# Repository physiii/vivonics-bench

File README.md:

# Vivonics Bench

Standalone hardware-bench repository for Vivonics shared-optical-metrology and
operator-material-screen work. The parent Vivonics repo consumes this
repository as its `bench/` Git submodule. It owns
both the Raspberry Pi measurement service and the ESP32-S3 laser-controller
firmware/circuit package.

The Pi owns the tight first-loop instrumentation:

- HDMI projector pattern display
- `IMX477` camera capture through `rpicam` / RTSP frame grabs
- USB-first control and telemetry for the ESP32-S3 four-source laser controller,
  with automatic Wi-Fi fallback
- optional `TSL2591` and `AS7341` I2C sensor snapshots
- later BPW34 photodiode data only after an ESP32/external ADC or TIA path

## Files

- `bench_service.py`: FastAPI service for projector/camera/sensor runs.
- `x1_measurement.py`: file-backed CLI smoke-test runner.
- `capture.py`, `projector.py`, `sensors.py`: hardware adapters.
- `laser_gpio.py`: Raspberry Pi GPIO outputs for red / green laser switching.
- `laser_controller_client.py`: persistent USB owner, normalized ADC telemetry,
  independent four-source control, and Wi-Fi fallback.
- `photocycle.py`: metrology and operator-screen red-linearity and green-write/red-read protocols.
- `install.sh`: user systemd service installer for `vivonics-bench`.
- `scripts/deploy_remote.sh`: workstation-to-Pi deploy helper.
- `laser_controller/`: authoritative ESP32-S3 firmware, KiCad design, review
  gates, and first-article support files for the fabricated laser controller.

## Install on the Pi

```bash
cd /home/andy/vivonics/pi  # standalone deployment path on the Pi
./install.sh
sudo raspi-config nonint do_i2c 0
```

`install.sh` creates a repo-local `.venv` so Raspberry Pi OS PEP 668 system
Python protection does not block dependency installation.

Check I2C sensor visibility:

```bash
/usr/sbin/i2cdetect -y 1
python3 x1_measurement.py sensor-check
```

Run the bench service:

```bash
./install.sh
curl http://raspberrypi.local:8090/status
curl http://raspberrypi.local:8090/sensors
```

## Laser GPIO Wiring

Use these Raspberry Pi BCM pins:

| Channel | BCM GPIO | Physical pin |
| --- | ---: | ---: |
| Red laser enable | `GPIO15` | `10` |
| Green laser enable | `GPIO24` | `18` |

Do not power or ground a laser module directly through a Pi GPIO pin. Use each
GPIO as a logic signal into a low-side MOSFET or transistor switch, with the
laser supply ground tied to Pi ground. The Pi pin drives the gate/base; laser
negative goes to the MOSFET drain / transistor collector; source / emitter goes
to ground. Keep the laser module's own current limiting or driver in place.

The camera-bench user service defaults to `VIVONICS_LIGHT_DRIVER=controller`.
It holds `/dev/ttyACM0` open, streams controller telemetry over USB, and falls
back to the current controller address at `http://192.168.1.110` when USB is
stale. The legacy GPIO path remains
available for older benches. It is active-high by default:
`Off` drives the pins low; red or green on drives the selected channel high. It
uses `10 kHz` PWM, mapping protocol levels `0..255` to `0..100%` active duty
cycle. Select the legacy path with `VIVONICS_LIGHT_DRIVER=gpio`; override pins with
`VIVONICS_RED_LASER_GPIO` and `VIVONICS_GREEN_LASER_GPIO`. Set
`VIVONICS_LASER_ACTIVE_HIGH=0` only for active-low driver hardware.

The current IR-capable USB operator camera needs explicit low-light preview
controls for the enclosed bench. Install
`systemd/50-usb-camera-demo-controls.conf` as a drop-in for
`c1-camera-rtsp.service`; it raises preview exposure and gain while keeping the
30 fps exposure envelope. This setting affects the USB RTSP/WebRTC operator
view only. It does not change direct IMX477 measurement capture.

Install `systemd/45-usb-camera-high-quality.conf` on the same service to
publish the camera's highest native real-time mode, `1920x1080 @ 30 fps`, at a
`20 Mbit/s` H.264 target. MediaMTX relays that stream to WebRTC without another
encode. The earlier `1280x720 @ 3 Mbit/s` publisher setting is not suitable for
the entropy of the low-light bench image and produces visible macroblocking.

## Reactor AD7606 Wiring and Bring-Up Notes

This is the working wiring map for the second Raspberry Pi bench
(`192.168.1.122`) that replaces the camera read path with BPW34 photodiodes
through an AD7606 module. It was brought up on `2026-05-25` on the second
reactor plane: `BUSY` began responding only after `CVA` and `CVB` were tied
together to the Pi conversion strobe.

Current reactor laser pins:

| Function | Raspberry Pi pin |
| --- | --- |
| Red laser 2N7000 gate | `GPIO15`, physical pin `10` |
| Second write laser 2N7000 gate (`green` in the service; may be blue in the reactor) | `GPIO24`, physical pin `18` |
| Infrared laser 2N7000 gate | `GPIO23`, physical pin `16` |
| Blue laser 2N7000 gate | `GPIO14`, physical pin `8` |
| 2N7000 sources / laser supply negative / ADC ground | Pi `GND`, common ground |

Observed AD7606 module digital header, top-to-bottom as shown by the board
silkscreen:

| Left column | Right column |
| --- | --- |
| `GND` | `+5V` |
| `OS1` | `OS0` |
| `RAGE` / `RANGE` | `OS2` |
| `CVB` | `CVA` |
| `RD` | `RST` |
| `BUSY` | `CS` |
| `FRST` | `VIO` |
| `DB1` | `DB0` |
| `DB3` | `DB2` |
| `DB5` | `DB4` |
| `DB7` | `DB6` |
| `DB9` | `DB8` |
| `DB11` | `DB10` |
| `DB13` | `DB12` |
| `DB15` | `DB14` |

Raspberry Pi top-down header map:

```text
Raspberry Pi 40-pin header, physical pin numbers.
Pin 1 is upper-left when looking down at the GPIO header.

 LEFT ROW                         RIGHT ROW
  1  3V3  -> AD7606 VIO           2  5V   -> AD7606 +5V
  3  GPIO2   unused               4  5V   optional +5V
  5  GPIO3   unused               6  GND  -> AD7606 GND/common
  7  GPIO4   -> AD7606 CVA+CVB    8  GPIO14 -> blue 2N7000 gate
  9  GND     common              10  GPIO15 -> red 2N7000 gate
 11  GPIO17  <- AD7606 DB0       12  GPIO18 <- AD7606 DB1
 13  GPIO27  <- AD7606 DB2       14  GND
 15  GPIO22  <- AD7606 DB3       16  GPIO23 -> infrared 2N7000 gate
 17  3V3     optional VIO        18  GPIO24 -> green 2N7000 gate
 19  GPIO10  <- AD7606 DB4       20  GND
 21  GPIO9   <- AD7606 DB5       22  GPIO25 <- AD7606 DB6
 23  GPIO11  <- AD7606 DB7       24  GPIO8  <- AD7606 DB8
 25  GND                         26  GPIO7  <- AD7606 DB9
 27  GPIO0   unused              28  GPIO1  unused
 29  GPIO5   <- AD7606 DB10      30  GND
 31  GPIO6   <- AD7606 DB11      32  GPIO12 <- AD7606 DB12
 33  GPIO13  <- AD7606 DB13      34  GND
 35  GPIO19  <- AD7606 DB14      36  GPIO16 <- AD7606 DB15
 37  GPIO26  <- AD7606 BUSY      38  GPIO20 -> AD7606 RD
 39  GND                         40  GPIO21 -> AD7606 RST
```

Fixed ADC pins:

| AD7606 pin | Draft connection | Reason |
| --- | --- | --- |
| `CS` | `GND` | Single ADC, always selected during bring-up. |
| `OS0`, `OS1`, `OS2` | `GND` | No oversampling for first tests. |
| `RAGE` / `RANGE` | `GND` | Start in the lower analog input range if supported by the module. |
| `FRST` | no connect | Optional first-data marker; not needed for first channel test. |
| `VIO` | Pi `3V3` | Keep ADC digital outputs at Pi-safe logic level. |

Do not connect or rework the AD7606 `DB0..DB15` outputs unless `VIO` is
confirmed to be tied to `3V3`; the Pi GPIO bus is not 5 V tolerant. The
validated bring-up sequence is: power the module, hold data pins as Pi inputs,
set `RD` inactive high, pulse `RST`, pulse tied `CVA`/`CVB`, confirm `BUSY`
returns low, then read the eight 16-bit parallel words.

For a one-channel BPW34 test, connect the photodiode resistor sense node to
`V1`, and connect the matching `G` input beside `V1` to the common ground. Even
when using only `V1`, the AD7606 digital read path still needs the 16-bit data
bus unless the module is separately configured for serial/SPI mode.

Verified reactor-plane response on `192.168.1.122`:

| Test state | ADC channel 1 mean | ADC channel 2 mean | Main observed delta |
| --- | ---: | ---: | --- |
| Lasers off before red test | `11214.9` | `29411.8` | baseline |
| `GPIO23` red laser at level `128` | `13622.8` | `29351.4` | `ch1 +2407.9` |
| Lasers off before second-laser test | `11220.6` | `29381.1` | baseline |
| `GPIO24` second laser at level `128` | `13927.3` | `29331.9` | `ch1 +2706.7` |

As currently wired, both laser controls produce the strongest positive optical
response on AD7606 channel `1`. Channel `2` is high at baseline but only shifts
by about `-50` to `-60` counts in these tests. Channels `3..8` stayed near zero.
The bench was left idle with both laser GPIOs off after the red test.

### 2026-05-26 Concentrated-Vial BPW34 / AD7606 Result

The concentrated-vial test did not produce an evidence-grade bR write/read
signal. The reactor bench hardware was working, but the read channel was
dominated by optical/electrical recovery from the green write pulse.

Key observed CH1 states with the concentrated vial:

| State | AD7606 CH1 mean | Notes |
| --- | ---: | --- |
| Lasers off | `11196` | dark/readout baseline |
| Red probe on | `29564` | strong red-path response |
| Green write on | `29497` | green also couples strongly into CH1 |
| Red + green on | `29618` | near the same high-count regime |

The best CH1-only direct capture ran at about `4.7 kHz`, enough to inspect the
sub-millisecond to tens-of-milliseconds bR window. In that run the immediate
green-write/red-probe bin showed about `+181` counts in `0-0.1 ms`, but the
red-off dark control showed about `+18,392` counts in the same bin. After
`0.5 ms`, the red-probe effect collapsed to the noise floor. A delayed red-read
check at `0`, `0.5`, `1`, `2`, `5`, and `10 ms` after green write did not show
a significant green-vs-control separation in the useful bins.

Artifacts from this run are in the parent workspace:

- `bench-output/reactor_direct_strong_vial_ch1fast_20260526T110410Z.json`
- `bench-output/reactor_direct_strong_vial_delayed_read_20260526T110611Z.json`

Interpretation: the AD7606 has enough code resolution for the current signal
levels; the blocker is not ADC bit depth. The BPW34 is sensitive to green light,
and the raw photodiode/resistor/ADC node stores charge when hit by the green
write pulse. That recovery transient can masquerade as an early read signal.

Next optical fixes, in priority order:

1. Add a red-pass or `650 nm` bandpass filter directly in front of the BPW34 so
   the detector sees the red probe but rejects the green write pulse.
2. Add black baffling, tubing, or a small aperture around the BPW34 so direct
   green scatter cannot reach the detector.
3. Keep paired controls for every run: green-write run, no-green control, and
   red-off dark control. A bR claim must survive all three.
4. Add a reference photodiode if possible, then subtract common laser drift and
   scattered-light pickup from the through-vial detector.

A TIA is still useful, but not because the ADC lacks resolution. A TIA can hold
the BPW34 near a fixed bias/virtual-ground point, lower the source impedance into
the AD7606, define the bandwidth with known feedback components, and recover
faster after a large light pulse. It can also support clamping or blanking during
the write pulse. A TIA will not, by itself, reject green light that physically
reaches the BPW34; optical filtering and baffling come first.

### 2026-05-26 No-Vial Green Leakage Control

After pulling the BPW34 back into the cavity to reduce side light, the vial was
removed and the reactor was tested with only laser light in the chamber. This is
the current negative control for deciding whether the immediate post-green
signal is protein or setup artifact.

No-vial CH1 steady states:

| State | AD7606 CH1 mean | Notes |
| --- | ---: | --- |
| Lasers off | `11497 +/- 191` | dark/readout baseline |
| Red probe on | `15352 +/- 189` | red path reaches CH1 |
| Green write on | `18036 +/- 195` | green still reaches CH1 strongly |
| Red + green on | `21852 +/- 191` | additive optical pickup |

The no-vial fast CH1 run reproduced the same immediate post-green transient that
appeared with the vial:

| Window | Red-probe sequence | Red-off dark control | Interpretation |
| --- | ---: | ---: | --- |
| `0-0.1 ms` | `+6372` | `+6377` | artifact, not protein |
| `0.1-0.25 ms` | `+4617` | `+4606` | artifact, not protein |
| `0.25-0.5 ms` | `+1666` | `+1635` | artifact, not protein |
| `0.5-1 ms` | `+424` | `+387` | artifact tail |

Because the same response appears with no vial and even in the red-off dark
control, the first sub-millisecond response cannot be used as bR evidence. The
exact sequence `green on -> green off -> red on` was also tested with delays of
`0`, `0.5`, `1`, `2`, `5`, and `10 ms`. After about `0.5-1 ms`, the no-vial
green-vs-control separation was mostly insignificant, but that is also the time
region where fast liquid-phase bR response may already be decaying.

Artifacts from this control were produced as local temp files:

- `/tmp/reactor_no_vial_ch1fast_20260526T114617Z.json`
- `/tmp/reactor_no_vial_delayed_read_20260526T114754Z.json`

Updated conclusion: BPW34 and AD7606 timing are not the main blocker. The
detector path is fast enough for millisecond-scale checks, but green write light
still reaches CH1 and creates detector/readout recovery that is larger than the
candidate bR readout. The next useful geometry target is that `green on` should
stay near the lasers-off CH1 baseline while `red on` remains clearly above it.
Use tighter black baffling/tubing/aperture first, then a red-pass or `650 nm`
filter directly in front of the BPW34.

Run a file-backed red linearity check:

```bash
python3 x1_measurement.py linearity --output-dir /tmp/vivonics_x1_linearity
```

Deploy from the workstation:

```bash
scripts/deploy_remote.sh andy@192.168.1.174 /home/andy/vivonics/pi
```

Claim boundary: these scripts are instrumentation for shared-optical-metrology
and operator-screen smoke tests. They do not promote Carolina `NRC-1` material to evidence-grade bR or purified
purple-membrane claims.

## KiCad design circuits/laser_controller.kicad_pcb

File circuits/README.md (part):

# Laser Controller — 1ch × 4λ: on-board SFH2201 PD → 4ch TIA + monitor-PD feedback + ESP32-S3 + 4× laser drivers

Bench controller for the bR index/phase read. **One optical channel, four wavelengths**
(IR / RED / GREEN / BLUE). Each wavelength has a precision **constant-current laser sink**
(with current-sense feedback) and one **on-board Osram SFH2201 clear Si PIN photodiode**
reverse-biased into an **OPA380 transimpedance amp**. The four TIA outputs go to the
on-board **AD7606BSTZ-4**. An **ESP32-S3-WROOM-1** real-time co-processor drives the 4 PWM laser
controls, reads the 4 current-sense voltages and 4 internal laser monitor-photodiode
voltages on its own ADC pins, issues hardware-timed **CONVST** to the AD7606, clocks the
AD7606 serial outputs, is programmed
and powered over **native USB (Mini-B)**, and talks to the Raspberry Pi over **UART**.

**Why a single PD per wavelength (not a quad/centroid PD):** the production reader is a
Gpixel line sensor doing a *per-pixel intensity* read, and the bench's dual-pinhole
interferometer is also a single-PD intensity read — so one broadband PD per beam is the
faithful, JLCPCB-assemblable proxy. Beam-deflection/centroid sensing (the quad-PD's only
unique capability) is a fallback the production engine deliberately engineers out. Rationale:
`../../docs/program/DUAL_PINHOLE_PHASE_READ_EXPERIMENT_DESIGN_2026-06-22.md`,
`SZEGED_BR_SWITCHING_LINEAGE_AND_INDEX_READ_FINDINGS_2026-06-22.md`,
`INDEX_READ_PRODUCTION_ARCHITECTURE_2026-06-02.md` (parent repo).

## Files

All sheets are **code-generated** from `gen_laser_controller.py`. The MCU sheet uses the
copied access-controller ESP32-S3 page with the real
`Espressif:ESP32-S3-WROOM-1` symbol, CP2102N USB-UART, two USB Mini-B entries,
discrete ESD/VBUS support, and reset/program/factory buttons. **Do not
hand-edit the generated `.kicad_sch` files**; edit the generator or copied-source
adapter flow deliberately and re-run:

```
python3 gen_laser_controller.py
```

| File | Role |
|---|---|
| `gen_laser_controller.py` | Generator for root, TIA, laser-driver, MCU, power/IO sheets + BOM. |
| `adapt_mcu.py` | Compatibility wrapper for older flows; it verifies the imported MCU sheet exists and does not overwrite the copied access-controller page. |
| `gen_pcb.py` | Placement-staging generator: keeps only the 90 x 50 mm board outline, stages schematic footprints outside the outline, and assigns PCB pad nets for manual placement/ratsnest work. |
| `check_laser_controller_pcb.py` | Board-level guardrail: verifies generated PCB pad nets against the exported schematic netlist. |
| `check_schematic_hierarchy_labels.py` | Schematic hierarchy/label guardrail: verifies root sheet pins, pin directions, child hierarchical label shapes, and intentional root global-label whitelist. |
| `check_schematic_presentation.py` | Schematic presentation guardrail: verifies generated net labels clear symbols/text/other labels, generated wires do not enter symbol bodies, and symbol pin anchors/strokes touch their glyphs. |
| `check_laser_controller_sources.py` | Source/register guardrail: verifies every exported MPN/LCSC token is represented in the source register or part notes, every exported net has a specific electrical-intent mapping, and every exported component pin has a component-pin-level role. |
| `check_part_notes_completeness.py` | Part-note guardrail: verifies critical datasheet notes still carry pinout, layout, risk, and checker-evidence phrases. |
| `check_source_documents.py` | Source-document guardrail: verifies required datasheet/manufacturer URLs and required local source/footprint artifacts are present; reports secondary/distributor source risks and vendor-CDN probe failures as warnings. |
| `check_laser_controller_release_gate.py` | Generated-copper fabrication gate: fails on split signal/control nets, unacceptable laser cathode/anode current routes, or missing laser sense-return GND vias; poured rail/zone connectivity is checked by KiCad refill/DRC. |
| `check_layout_review_geometry.py` | Focused layout-geometry gate for buck local loops, USB ESD placement, OPA380 summing-node loops, monitor-PD raw paths, and laser-current sense loops. |
| `check_laser_controller_release_readiness.py` | Open first-article/production blocker gate: keeps calibration, firmware, thermal, protection, procurement, and measured bring-up blockers visible in the review wrapper. |
| `check_jlcpcb_order_package.py` | JLCPCB prototype order-package gate: verifies Gerber/drill zip contents, BOM/POS designator match, J7 C192300 2x4 SMD header metadata, required board labels, the flat transfer archive, and the U1-U4/RV1-RV8 physical orientation gate. |
| `check_power_thermal_budget.py` | AP2112 `+3V3` thermal guardrail for bench/no-RF versus sustained RF policies. |
| `check_power_bringup_template.py` | First-article power/input bring-up measurement-template guardrail for J5/VIN24, AP632 rails, post-OR +5V, LASER_V+, and AP2112 +3V3 rows. |
| `check_vin24_input_protection.py` | VIN_24V bench-topology and production input-protection guardrail for J5/J6, adapter/harness limit, fuse/TVS/reverse-protection decisions. |
| `check_laser_driver_control_loop.py` | Laser-driver control-loop guardrail for PWM divider topology, TLV9001 input/output range, AO3400A gate drive, and the hardware-clamp gate-margin expected fail. |
| `check_laser_driver_package_pcb.py` | Laser-driver package/PCB guardrail: verifies U5-U8 TLV9001 and Q1-Q4 AO3400A schematic pin nets, local sense/command/gate/compensation component identities, current PCB pad nets, and KiCad SOT-23-5/SOT-23/2512/0603/0402/0603-cap geometry. |
| `check_laser_diode_footprints.py` | Direct LD1-LD4 TO-can guardrail: verifies selected diode MPN/footprint identities, schematic pin nets, current PCB pad nets, LD4 case no-connect, `MPD_RAW4` spare/open, and installed KiCad TO18/TO56 pad geometry. |
| `check_orientation_polarity_pcb.py` | Physical orientation/polarity guardrail for the mirror-risk parts found in the JLCPCB preview: U1-U4 OPA380 SOIC-8 pad order/rotation/pin nets and RV1-RV8 Bourns 3224W wiper geometry/nets. |
| `repair_orientation_sensitive_footprints.py` | Narrow, idempotent repair script for the confirmed mirrored U1-U4 OPA380 and RV5-RV8 Bourns 3224W embedded PCB footprints and directly attached local escape routing. |
| `check_monitor_pd_package_pcb.py` | Monitor-PD package/PCB guardrail: verifies U12 INA4180/U13 LM4040 pin nets, local 240 ohm sense, 1 k / 100 nF ADC filters, R41/C35/C36 support parts, current PCB pad nets, LD4 case no-connect, and KiCad TSSOP-14/SOT-23/0603/0402 geometry. |
| `check_laser_current_budget.py` | Laser current-loop guardrail for the PWM clamp, selected laser-diode current limits, sense resistor, AO3400A heat, and `LASER_V+` headroom. |
| `check_laser_bringup_template.py` | First-article laser bring-up measurement-template guardrail for LD1-LD4 current-limit, safety-fixture, optical-output, temperature, and firmware-shutoff rows. |
| `check_tia_readout_budget.py` | SFH2201/OPA380 signal-PD TIA guardrail: exact topology into AD7606, VBIAS/common-mode bound, OPA380 output headroom, and bright-ambient expected-fail range check. |
| `check_optical_calibration_template.py` | First-article optical/readout calibration-template guardrail for LD1-LD4 monitor-PD handling, D1-D4 signal-PD calibration, and U14 V1-V4 AD7606 known-input readback rows. |
| `check_firmware_validation_template.py` | First-article AD7606 firmware/readback validation-template guardrail for timing, both DOUT lines, scaling, channel order, and known-input rows. |
| `check_ad7606_package_pcb.py` | AD7606 package/PCB guardrail: verifies U14 schematic pin nets, C51-C60 AVCC/VDRIVE/REGCAP/reference capacitor identities and pad nets, current PCB pad nets, FRSTDATA no-connect, and installed KiCad LQFP-64 pad geometry. |
| `check_ap6320x_package_pcb.py` | AP63205/AP63200 package/PCB guardrail: verifies U15/U16 schematic pin nets, current PCB pad nets, KiCad TSOT-23-6 pad geometry, and local L1/L2 inductor footprint geometry. |
| `check_passive_derating.py` | Passive voltage/power guardrail for every assembled capacitor, resistor, and SMD trimmer MPN in the exported netlist. |
| `check_procurement_release_template.py` | Quote-time procurement and production-derating template guardrail for BOM/POS quote acceptance, substitutions, pulse/surge derating, board-temperature evidence, and order archive linkage. |
| `check_first_article_release_evidence.py` | First-article release evidence ledger guardrail: requires explicit closure rows for all deferred blocker categories and keeps them open until linked measurement/procurement/firmware evidence exists. |
| `run_laser_controller_review.py` | One-command review wrapper for available gates, JLCPCB order status, deferred first-article/production blockers, and KiCad ERC/DRC/parity reporting. |
| `laser_controller.kicad_sch` | Root sheet — sheet symbols + global-label interconnect (A2). |
| `tia_ir.kicad_sch`, `tia_red.kicad_sch`, `tia_green.kicad_sch`, `tia_blue.kicad_sch` | Four on-board PD + OPA380 TIA sheets with globally unique designators. |
| `laser_ir.kicad_sch`, `laser_red.kicad_sch`, `laser_green.kicad_sch`, `laser_blue.kicad_sch` | Four constant-current laser sink sheets with globally unique designators; each sheet has a direct through-hole TO-can footprint so `LD_K`, common `LD_A/PD_K/case`, and `PD_A -> MPD_RAW` are visible. |
| `mcu.kicad_sch` | ESP32-S3-WROOM-1 + CP2102N USB-UART + two USB Mini-B connectors + discrete USB/VBUS ESD + reset/program/factory buttons. |
| `power_io.kicad_sch` | 5V OR-ing, laser supply, on-board AD7606-4 signal ADC, and shared INA4180/LM4040 monitor-PD front end. |
| `laser_controller_bom_jlcpcb.csv` | JLCPCB assembly CSV (Comment, Designator, Footprint, LCSC) for SMT plus the J5/J6 through-hole connector assembly rows; direct laser cans are listed separately. |
| `fab/laser_controller_pos.csv` | JLCPCB CPL CSV converted to the five-column upload format (`Designator,Mid X,Mid Y,Layer,Rotation`); designators match the JLCPCB BOM. |
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
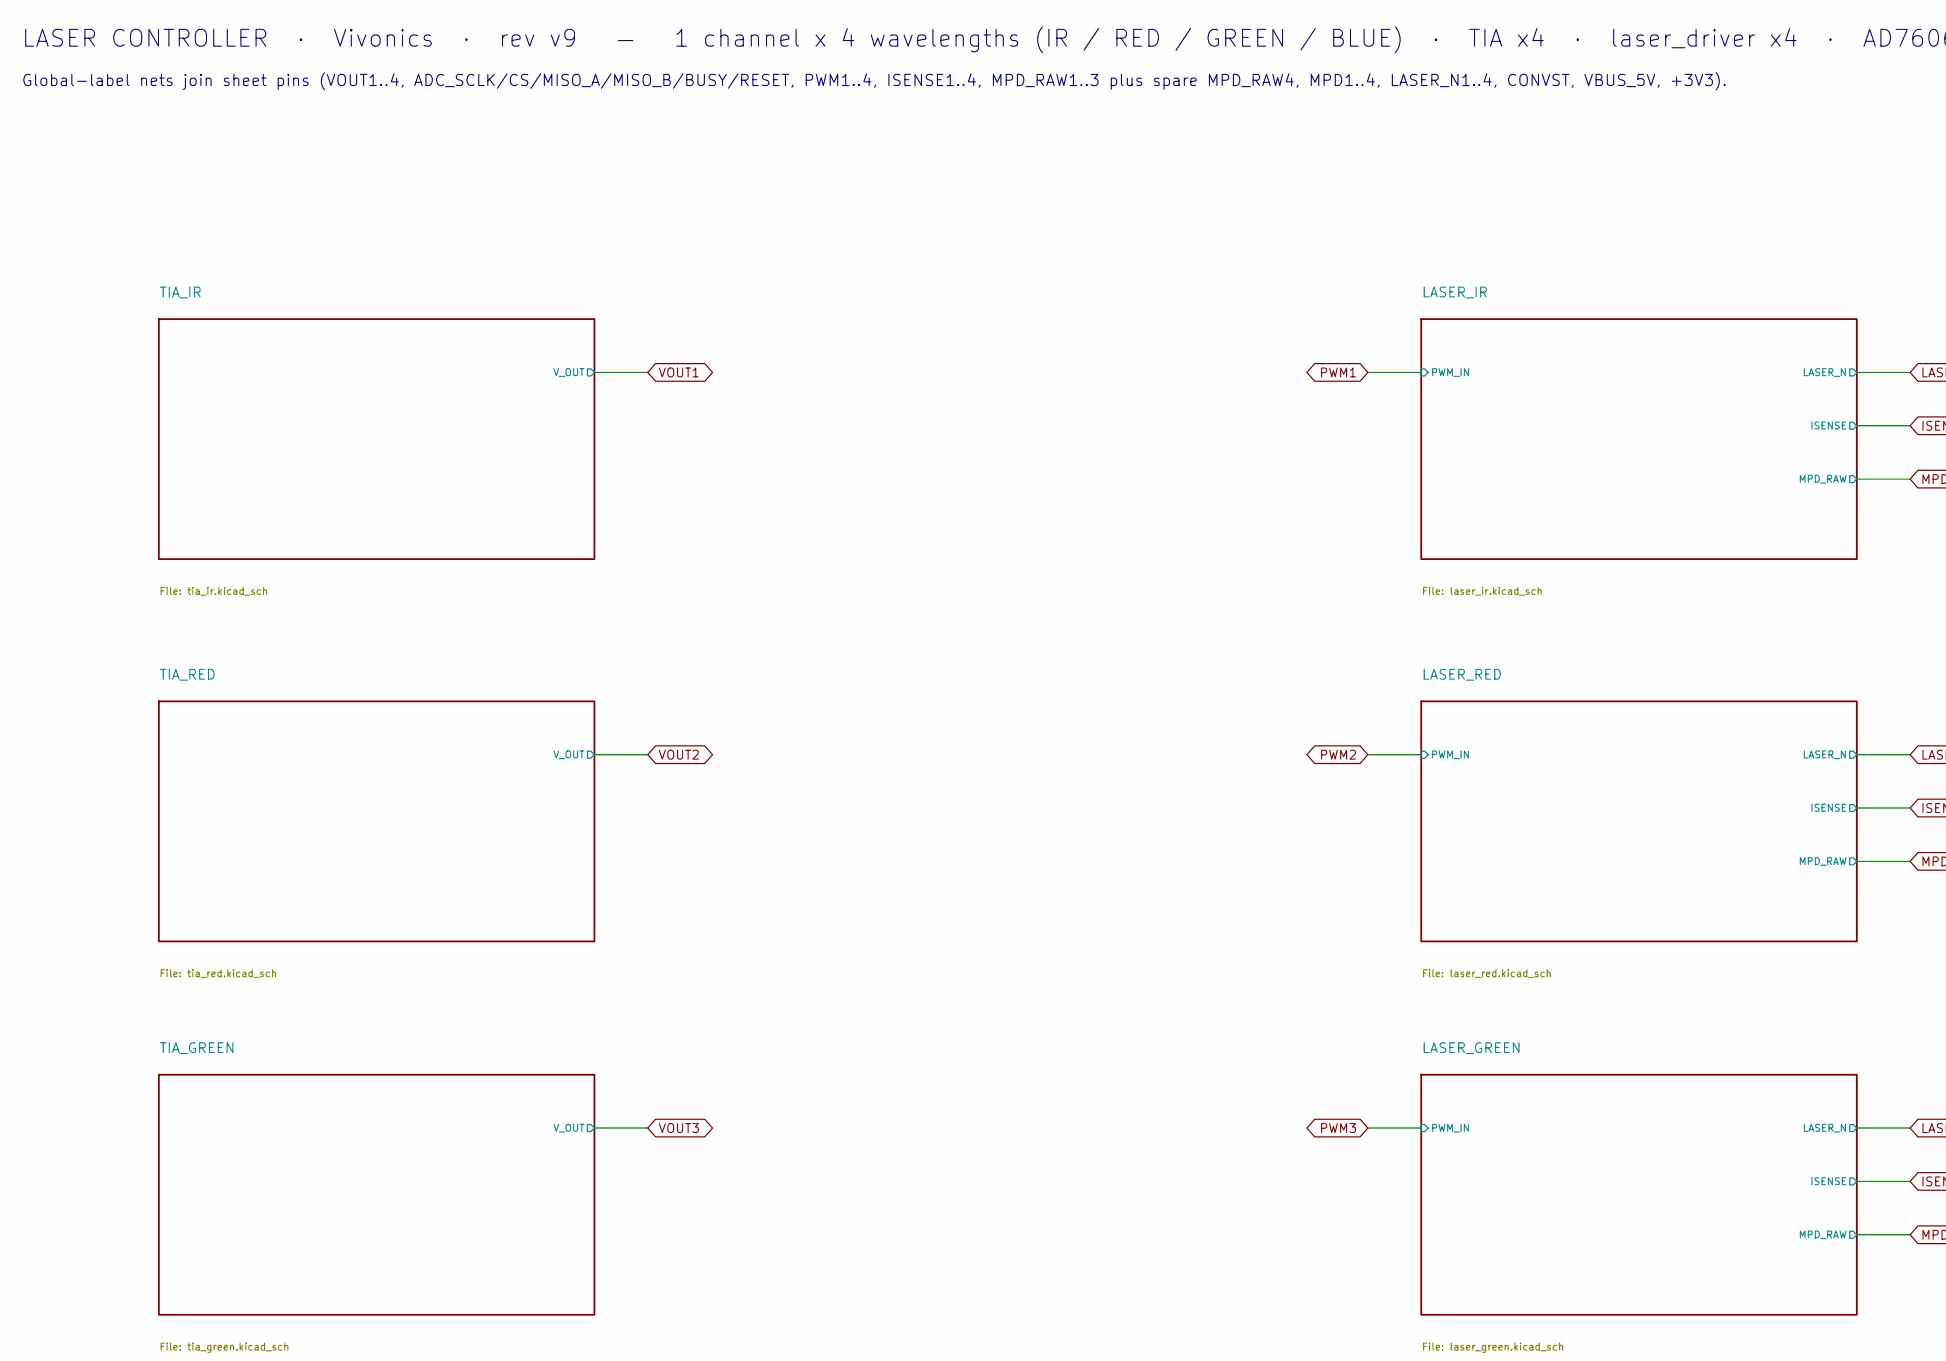
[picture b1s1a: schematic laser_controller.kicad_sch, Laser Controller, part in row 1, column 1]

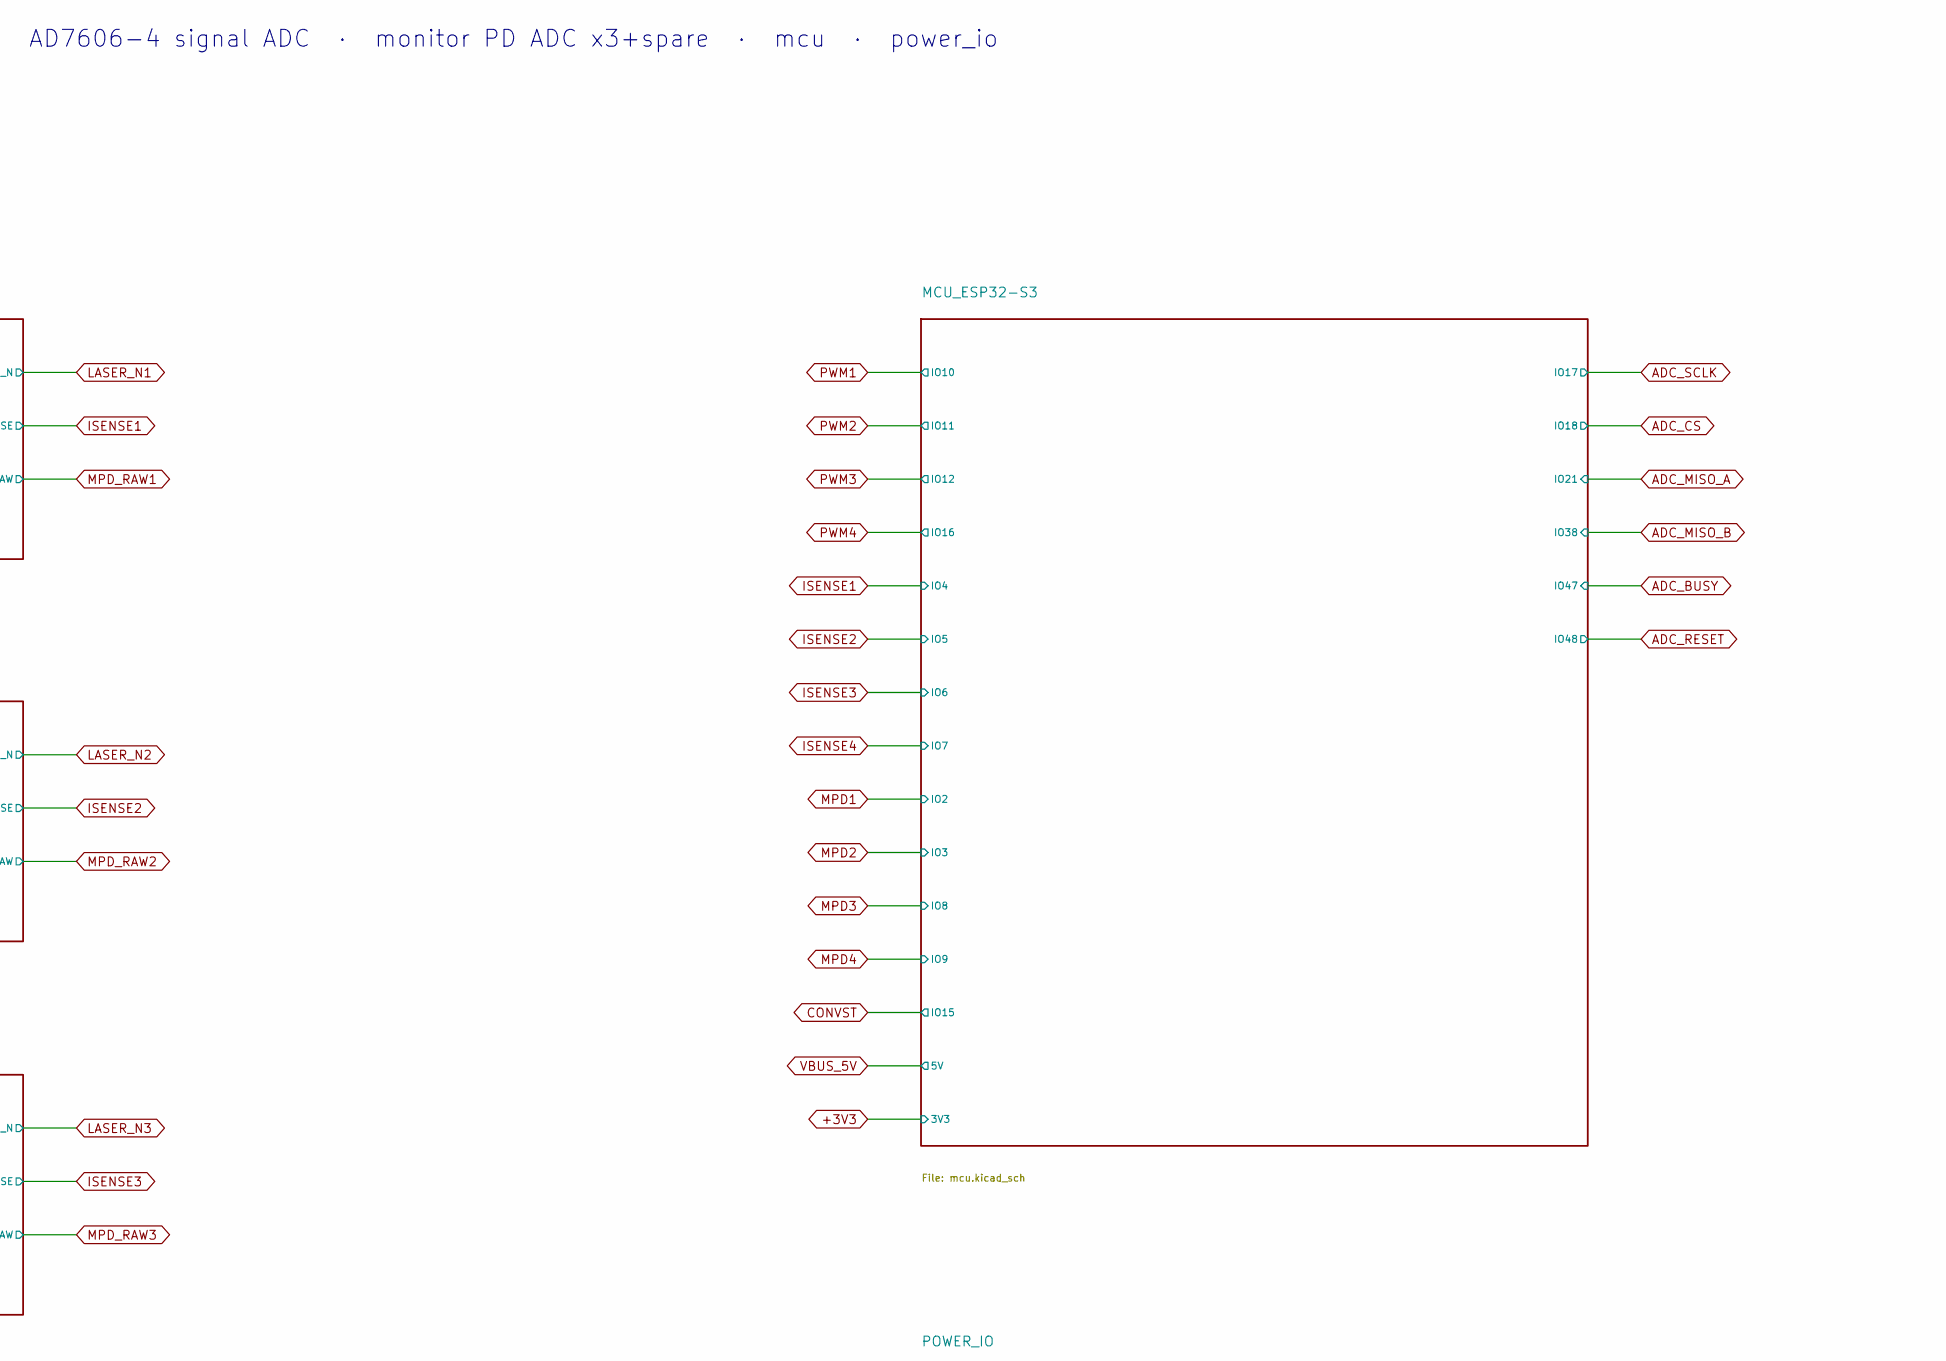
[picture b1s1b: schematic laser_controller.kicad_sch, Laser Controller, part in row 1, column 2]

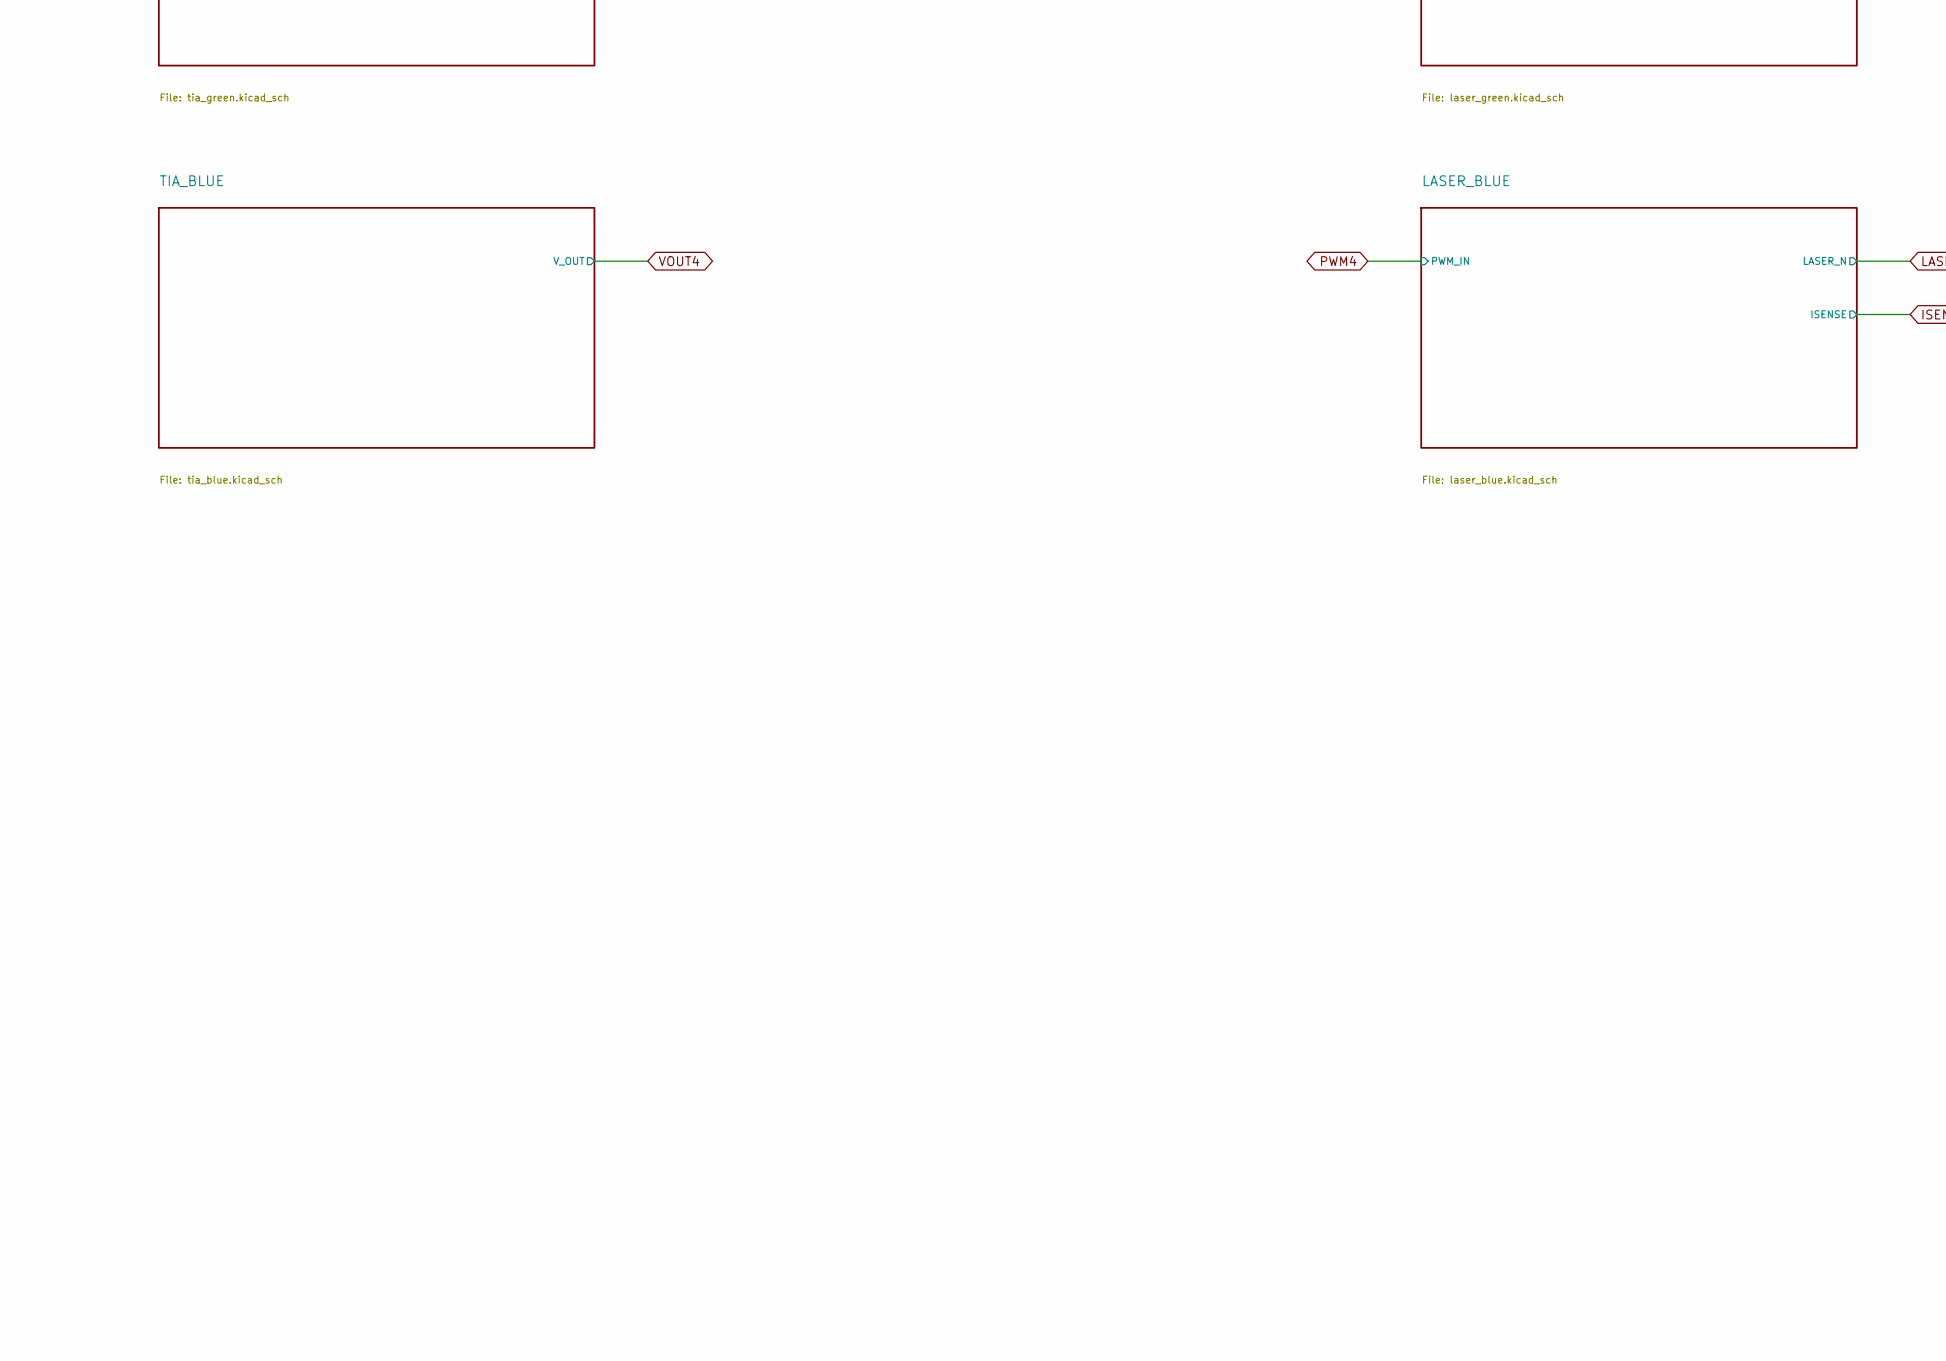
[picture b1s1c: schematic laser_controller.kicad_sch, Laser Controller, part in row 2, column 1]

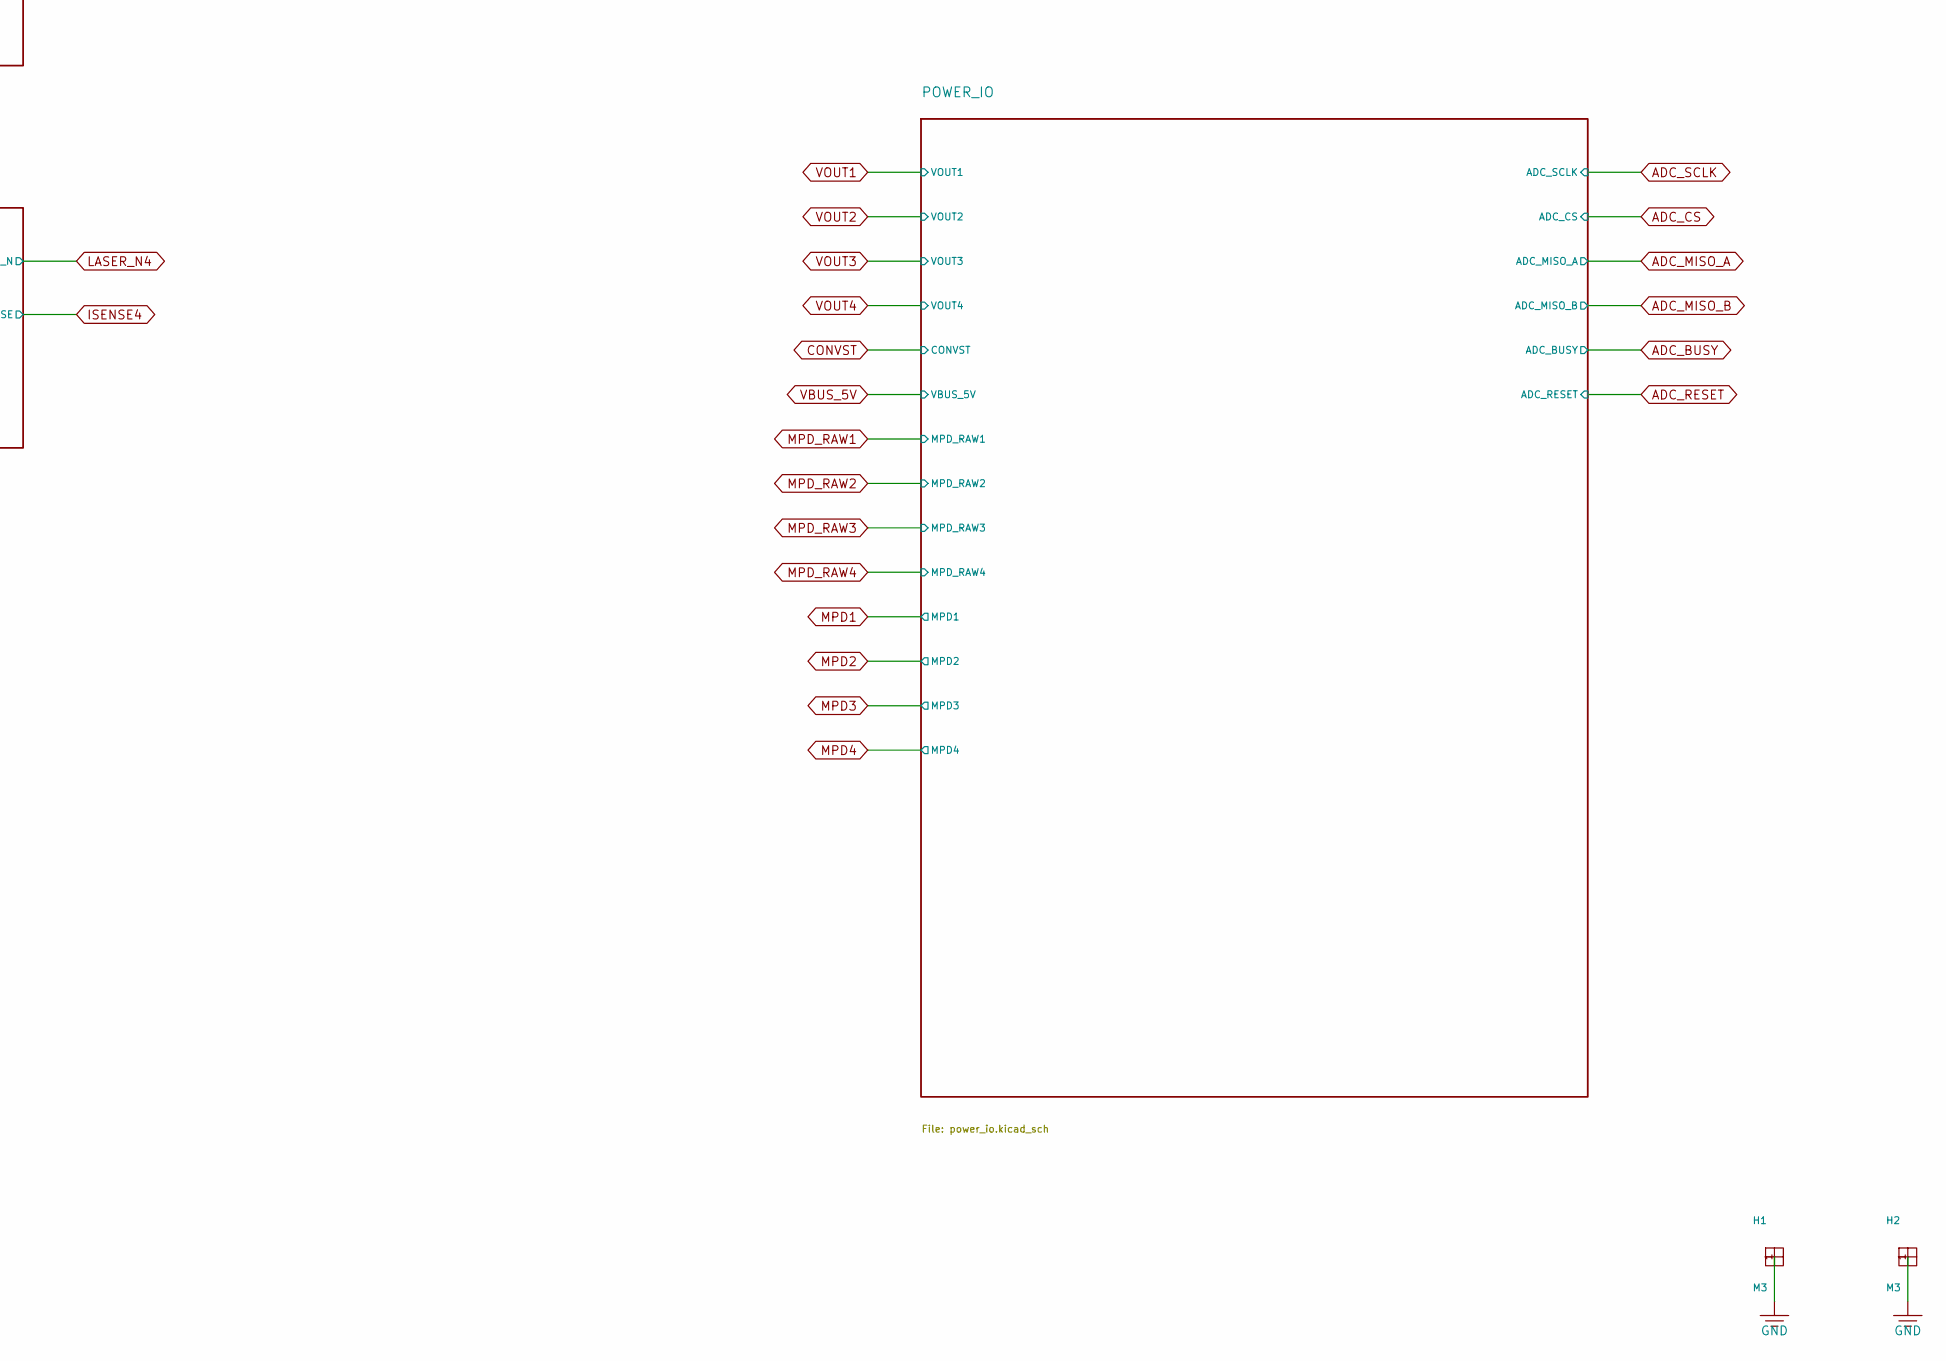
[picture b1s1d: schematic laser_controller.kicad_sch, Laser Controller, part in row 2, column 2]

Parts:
H1, H2: M3; MountingHole_3.2mm_M3

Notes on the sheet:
LASER CONTROLLER · Vivonics · rev v9 — 1 channel x 4 wavelengths (IR / RED / GREEN / BLUE) · TIA x4 · laser_driver x4 · AD7606-4 signal ADC · monitor PD ADC x3+spare · mcu · power_io
Global-label nets join sheet pins (VOUT1..4, ADC_SCLK/CS/MISO_A/MISO_B/BUSY/RESET, PWM1..4, ISENSE1..4, MPD_RAW1..3 plus spare MPD_RAW4, MPD1..4, LASER_N1..4, CONVST, VBUS_5V, +3V3).

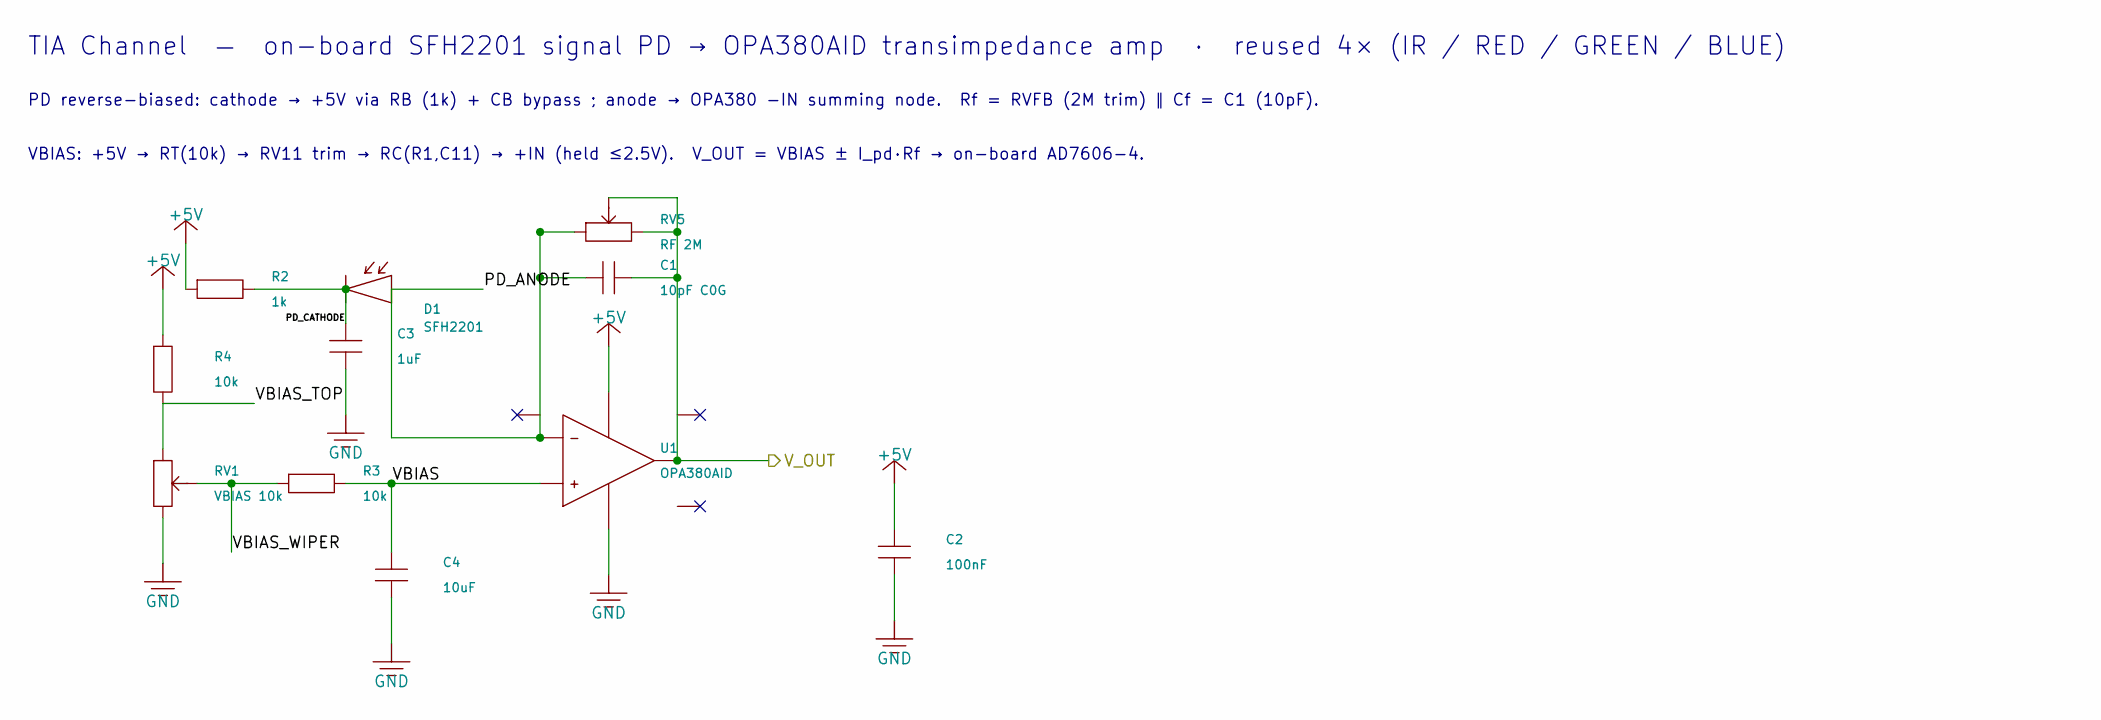
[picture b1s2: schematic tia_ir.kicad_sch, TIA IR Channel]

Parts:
C1: 10pF C0G; C_0603_1608Metric_Pad1.08x0.95mm_HandSolder; Part Number CC0603JRNPO9BN100; LCSC C106245
C2: 100nF; C_0402_1005Metric_Pad0.74x0.62mm_HandSolder; Part Number 0402B104K160CT; LCSC C83056
C3: 1uF; C_0402_1005Metric_Pad0.74x0.62mm_HandSolder; Part Number HGC0402R5105K250NTEJ; LCSC C7472946
C4: 10uF; C_0805_2012Metric_Pad1.18x1.45mm_HandSolder; Part Number CL21A106KAYNNNG; LCSC C318691
D1: SFH2201; Osram_SFH2201; Part Number SFH2201; LCSC C2900216
R2: 1k; R_0603_1608Metric_Pad0.98x0.95mm_HandSolder; Part Number FRC0603F1001TS; LCSC C2907002
R3, R4: 10k; R_0603_1608Metric_Pad0.98x0.95mm_HandSolder; Part Number CRCW060310K0FKEA; LCSC C844918
RV1: VBIAS 10k; Potentiometer_Bourns_3224W_Vertical; Part Number 3224W-1-103E; LCSC C81348
RV5: RF 2M; Potentiometer_Bourns_3224W_Vertical; Part Number 3224W-1-205E; LCSC C116323
U1: OPA380AID; SOIC-8_3.9x4.9mm_P1.27mm; Part Number OPA380AID; LCSC C201677

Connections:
/TIA_IR/PD_ANODE: C1.1, D1.2 (A), RV5.1, U1.2 (-)
/TIA_IR/PD_CATHODE: C3.1, D1.1 (K), R2.2
/TIA_IR/VBIAS: C4.1, R3.2, U1.3 (+)
/TIA_IR/VBIAS_TOP: R4.2, RV1.1
/TIA_IR/VBIAS_WIPER: R3.1, RV1.2 (W)
VOUT1: C1.2, RV5.2 (W), RV5.3, U1.6; also elsewhere on the board

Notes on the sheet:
TIA Channel — on-board SFH2201 signal PD → OPA380AID transimpedance amp · reused 4× (IR / RED / GREEN / BLUE)
PD reverse-biased: cathode → +5V via RB (1k) + CB bypass ; anode → OPA380 −IN summing node. Rf = RVFB (2M trim) ∥ Cf = C1 (10pF).
VBIAS: +5V → RT(10k) → RV11 trim → RC(R1,C11) → +IN (held ≤2.5V). V_OUT = VBIAS ± I_pd·Rf → on-board AD7606-4.

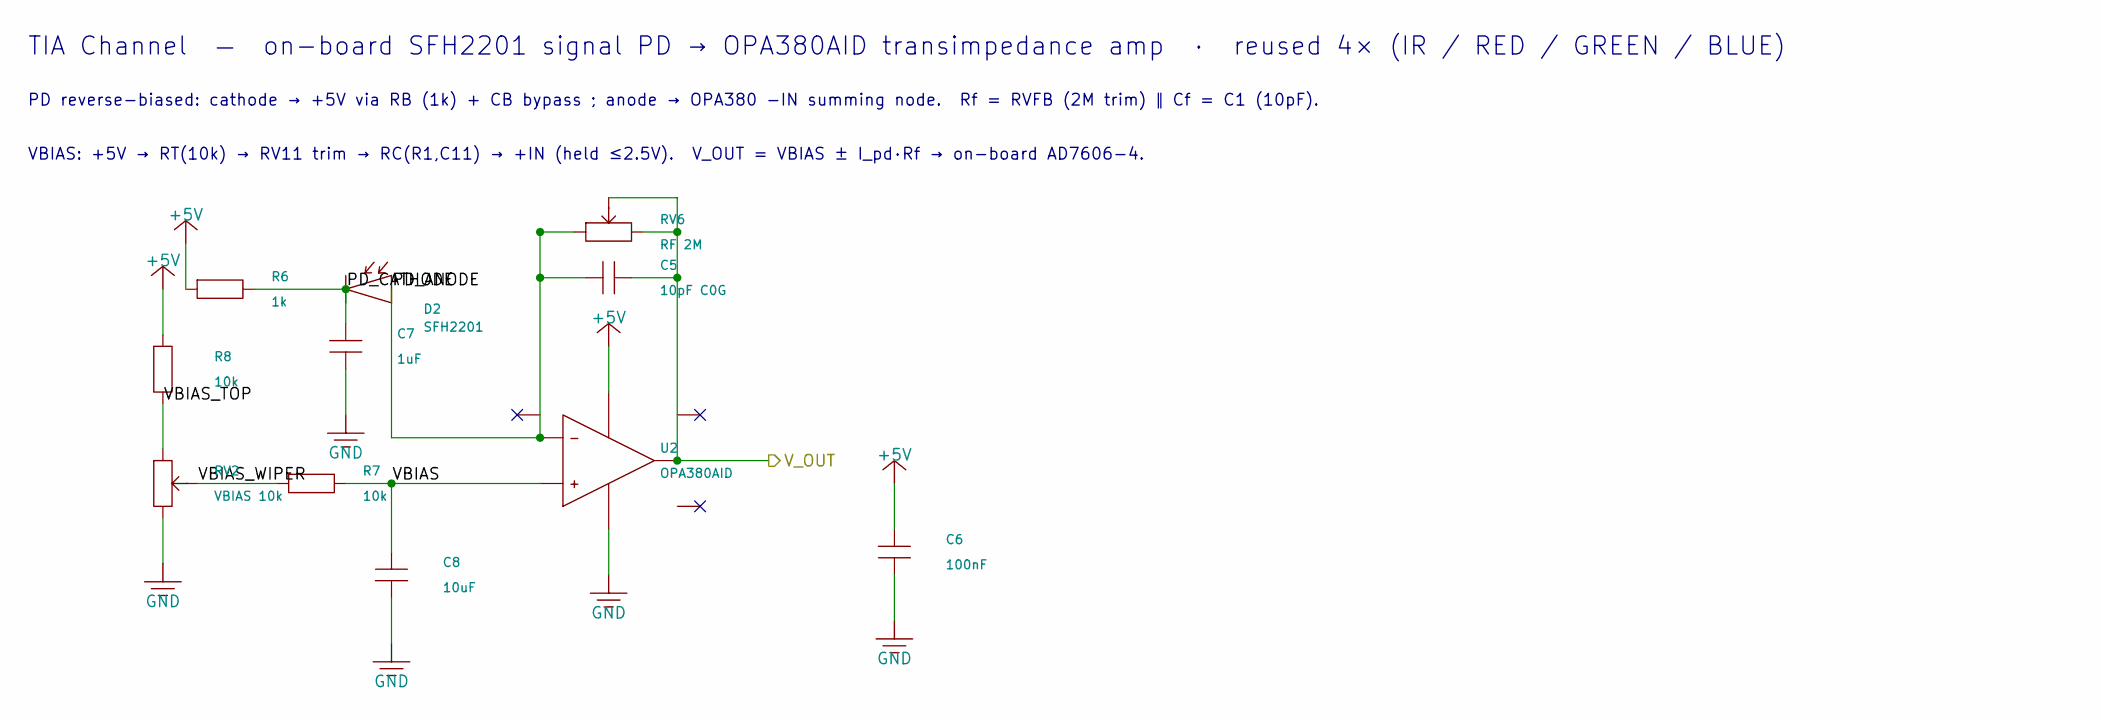
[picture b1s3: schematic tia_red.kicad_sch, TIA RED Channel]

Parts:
C5: 10pF C0G; C_0603_1608Metric_Pad1.08x0.95mm_HandSolder; Part Number CC0603JRNPO9BN100; LCSC C106245
C6: 100nF; C_0402_1005Metric_Pad0.74x0.62mm_HandSolder; Part Number 0402B104K160CT; LCSC C83056
C7: 1uF; C_0402_1005Metric_Pad0.74x0.62mm_HandSolder; Part Number HGC0402R5105K250NTEJ; LCSC C7472946
C8: 10uF; C_0805_2012Metric_Pad1.18x1.45mm_HandSolder; Part Number CL21A106KAYNNNG; LCSC C318691
D2: SFH2201; Osram_SFH2201; Part Number SFH2201; LCSC C2900216
R6: 1k; R_0603_1608Metric_Pad0.98x0.95mm_HandSolder; Part Number FRC0603F1001TS; LCSC C2907002
R7, R8: 10k; R_0603_1608Metric_Pad0.98x0.95mm_HandSolder; Part Number CRCW060310K0FKEA; LCSC C844918
RV2: VBIAS 10k; Potentiometer_Bourns_3224W_Vertical; Part Number 3224W-1-103E; LCSC C81348
RV6: RF 2M; Potentiometer_Bourns_3224W_Vertical; Part Number 3224W-1-205E; LCSC C116323
U2: OPA380AID; SOIC-8_3.9x4.9mm_P1.27mm; Part Number OPA380AID; LCSC C201677

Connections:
/TIA_RED/PD_ANODE: C5.1, D2.2 (A), RV6.1, U2.2 (-)
/TIA_RED/PD_CATHODE: C7.1, D2.1 (K), R6.2
/TIA_RED/VBIAS: C8.1, R7.2, U2.3 (+)
/TIA_RED/VBIAS_TOP: R8.2, RV2.1
/TIA_RED/VBIAS_WIPER: R7.1, RV2.2 (W)
VOUT2: C5.2, RV6.2 (W), RV6.3, U2.6; also elsewhere on the board

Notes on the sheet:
TIA Channel — on-board SFH2201 signal PD → OPA380AID transimpedance amp · reused 4× (IR / RED / GREEN / BLUE)
PD reverse-biased: cathode → +5V via RB (1k) + CB bypass ; anode → OPA380 −IN summing node. Rf = RVFB (2M trim) ∥ Cf = C1 (10pF).
VBIAS: +5V → RT(10k) → RV11 trim → RC(R1,C11) → +IN (held ≤2.5V). V_OUT = VBIAS ± I_pd·Rf → on-board AD7606-4.
